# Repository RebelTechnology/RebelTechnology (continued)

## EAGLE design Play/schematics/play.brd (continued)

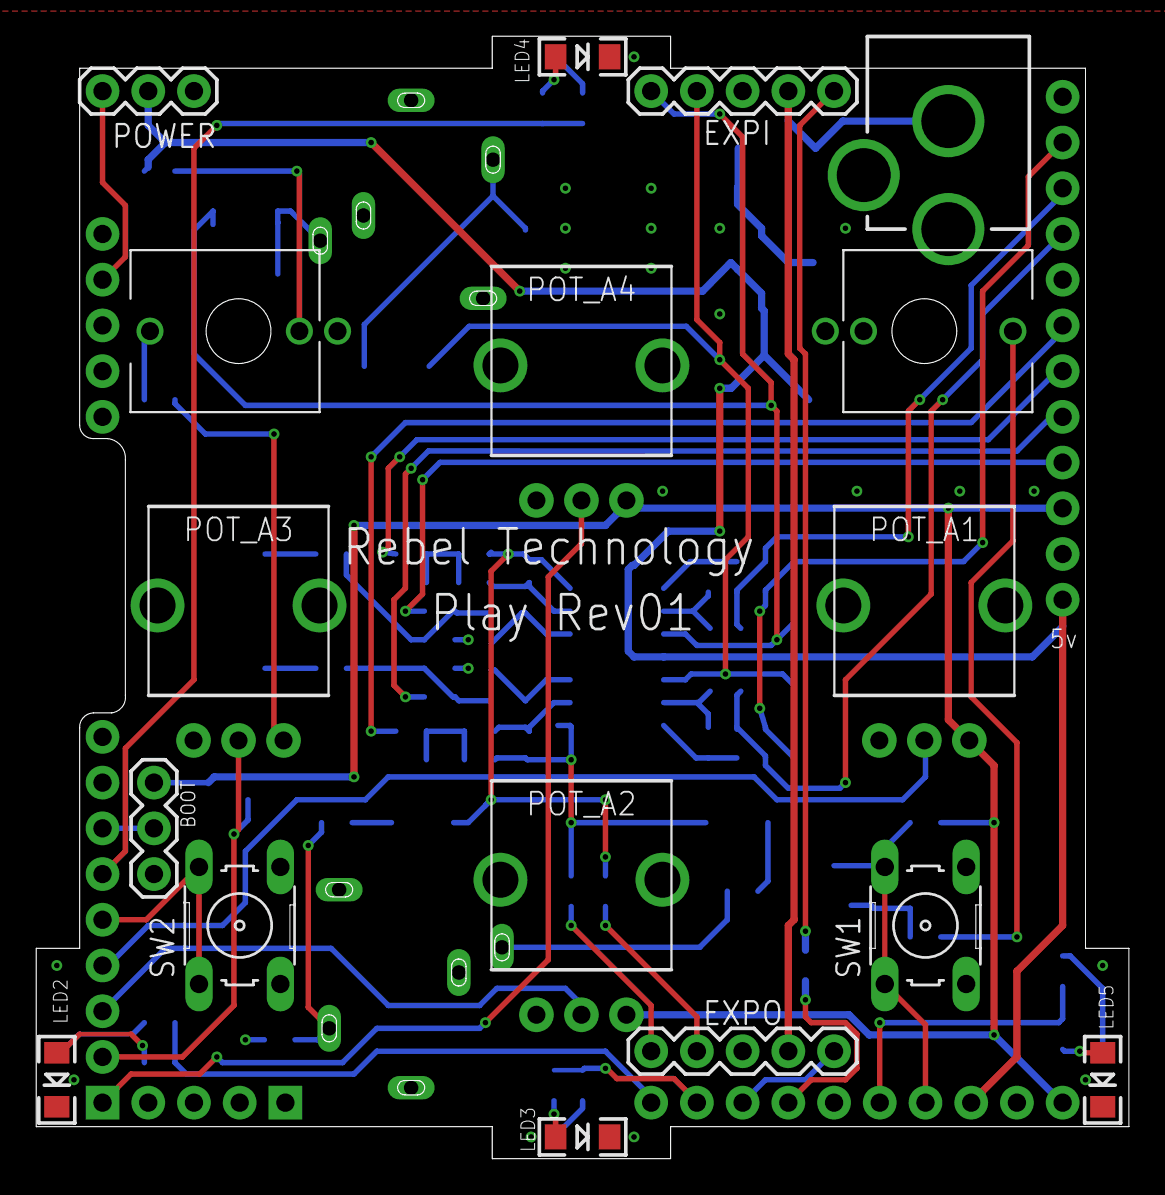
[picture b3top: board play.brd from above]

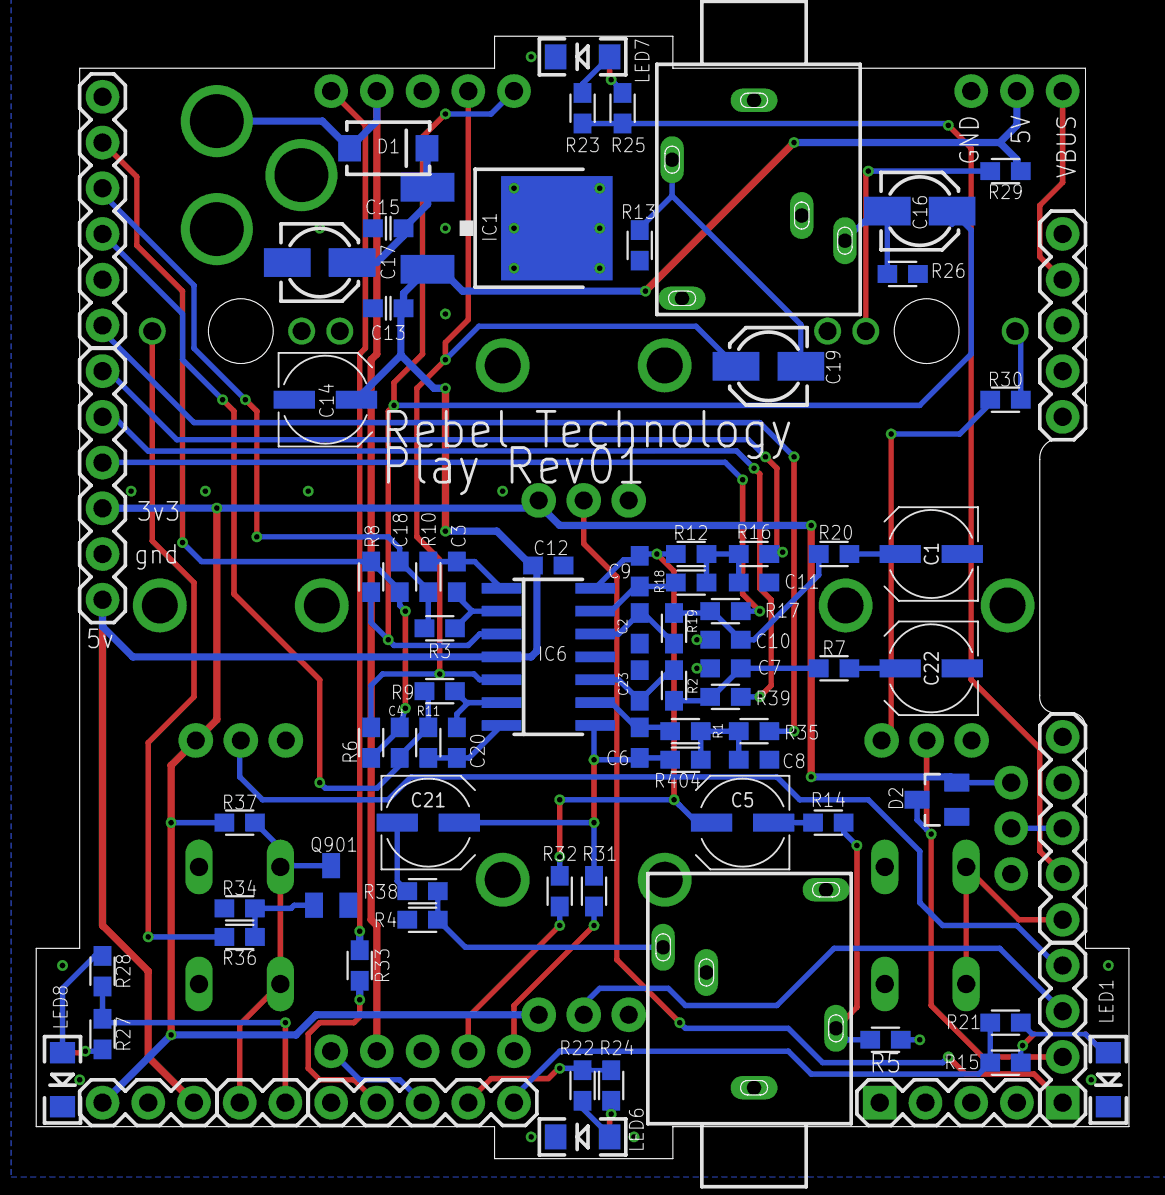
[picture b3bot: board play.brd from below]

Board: 2 copper layers, 60.7 x 62.4 mm, 100 parts (83 on the bottom side), 66 nets.

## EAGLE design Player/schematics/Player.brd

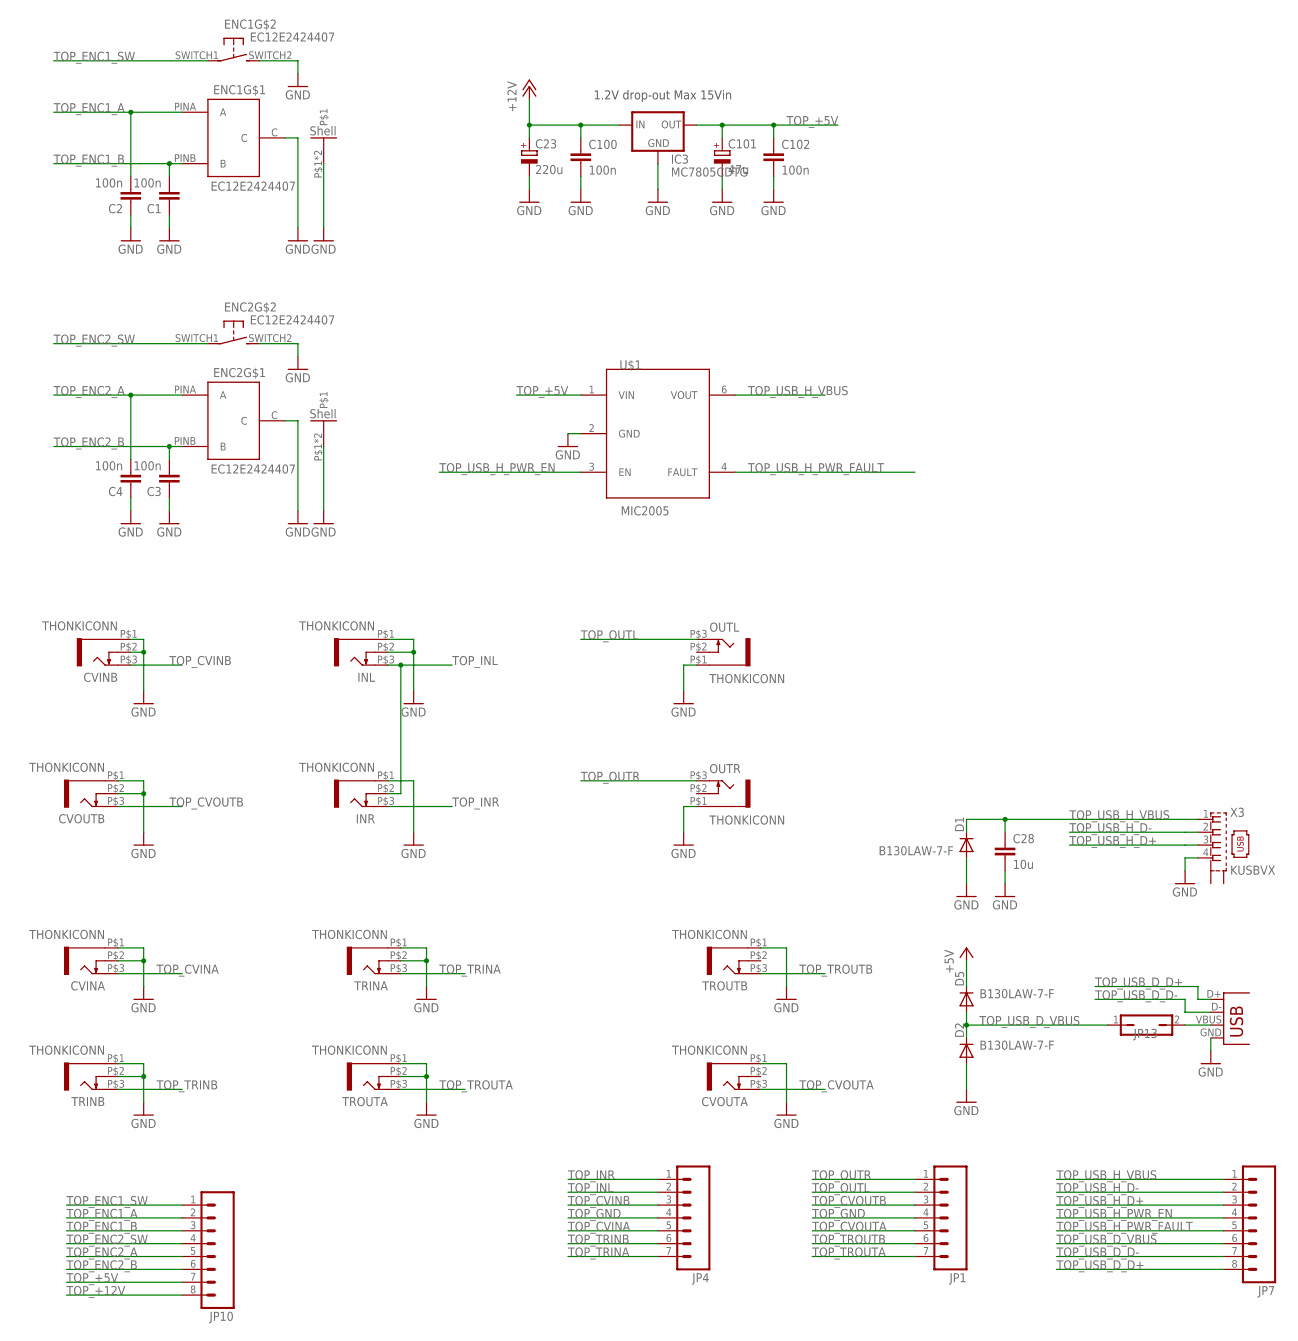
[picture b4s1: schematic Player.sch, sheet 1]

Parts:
C1, C2, C3, C4, C100, C102: 100n; C0603
C23: 220u; PANASONIC_D
C28: 10u; C1206
C101: 47u; CPOL-5
CVINA: THONKICONN
CVINB: THONKICONN
CVOUTA: THONKICONN
CVOUTB: THONKICONN
D1, D2, D5: B130LAW-7-F; SOD123
ENC1, ENC2: EC12E2424407
IC3: MC7805CDTG; DPACK
INL: THONKICONN
INR: THONKICONN
JP1, JP4: M07; 1X07
JP7, JP10: M081X08; 1X08
JP13: JP1Q; JP1
OUTL: THONKICONN
OUTR: THONKICONN
TRINA: THONKICONN
TRINB: THONKICONN
TROUTA: THONKICONN
TROUTB: THONKICONN
U$1: MIC2005; SOT23-6
X3: KUSBVX
X5: USBPTH-VERTICAL; USB-B-PTH-VERTICAL

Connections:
unnamed: JP13.2, X5.VBUS
TOP_+5V: C101.+, C102.1, D5.C, IC3.3 (OUT), JP10.7, U$1.1 (VIN)
TOP_+12V: C23.+, C100.1, IC3.1 (IN), JP10.8
TOP_CVINA: CVINA.P$3 (3), JP4.5
TOP_CVINB: CVINB.P$3 (3), JP4.3
TOP_CVOUTA: CVOUTA.P$3 (3), JP1.5
TOP_CVOUTB: CVOUTB.P$3 (3), JP1.3
TOP_ENC1_A: C2.2, ENC1.PINA (A), JP10.2
TOP_ENC1_B: C1.2, ENC1.PINB (B), JP10.3
TOP_ENC1_SW: ENC1.SWITCH1, JP10.1
TOP_ENC2_A: C4.2, ENC2.PINA (A), JP10.5
TOP_ENC2_B: C3.2, ENC2.PINB (B), JP10.6
TOP_ENC2_SW: ENC2.SWITCH1, JP10.4
TOP_GND: C1.1, C2.1, C3.1, C4.1, C23.-, C28.2, C100.2, C101.-, C102.2, CVINA.P$1 (5), CVINA.P$2 (4), CVINB.P$1 (5), CVINB.P$2 (4), CVOUTA.P$1 (5), CVOUTB.P$1 (5), CVOUTB.P$2 (4), D1.A, D2.A, ENC1.C, ENC1.P$1, ENC1.P$2, ENC1.SWITCH2 (S), ENC2.C, ENC2.P$1, ENC2.P$2, ENC2.SWITCH2 (S), IC3.4 (GND), INL.P$1 (5), INL.P$2 (4), INR.P$1 (5), JP1.4, JP4.4, OUTL.P$1 (5), OUTR.P$1 (5), TRINA.P$1 (5), TRINA.P$2 (4), TRINB.P$1 (5), TRINB.P$2 (4), TROUTA.P$1 (5), TROUTA.P$2 (4), TROUTB.P$1 (5), U$1.2 (GND), X3.4, X5.GND
TOP_INL: INL.P$3 (3), INR.P$2 (4), JP4.2
TOP_INR: INR.P$3 (3), JP4.1
TOP_OUTL: JP1.2, OUTL.P$3 (3)
TOP_OUTR: JP1.1, OUTR.P$3 (3)
TOP_TRINA: JP4.7, TRINA.P$3 (3)
TOP_TRINB: JP4.6, TRINB.P$3 (3)
TOP_TROUTA: JP1.7, TROUTA.P$3 (3)
TOP_TROUTB: JP1.6, TROUTB.P$3 (3)
TOP_USB_D_D+: JP7.8, X5.D+
TOP_USB_D_D-: JP7.7, X5.D-
TOP_USB_D_VBUS: D2.C, D5.A, JP7.6, JP13.1
TOP_USB_H_D+: JP7.3, X3.3
TOP_USB_H_D-: JP7.2, X3.2
TOP_USB_H_PWR_EN: JP7.4, U$1.3 (EN)
TOP_USB_H_PWR_FAULT: JP7.5, U$1.4 (FAULT)
TOP_USB_H_VBUS: C28.1, D1.C, JP7.1, U$1.6 (VOUT), X3.1

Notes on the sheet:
1.2V drop-out Max 15Vin

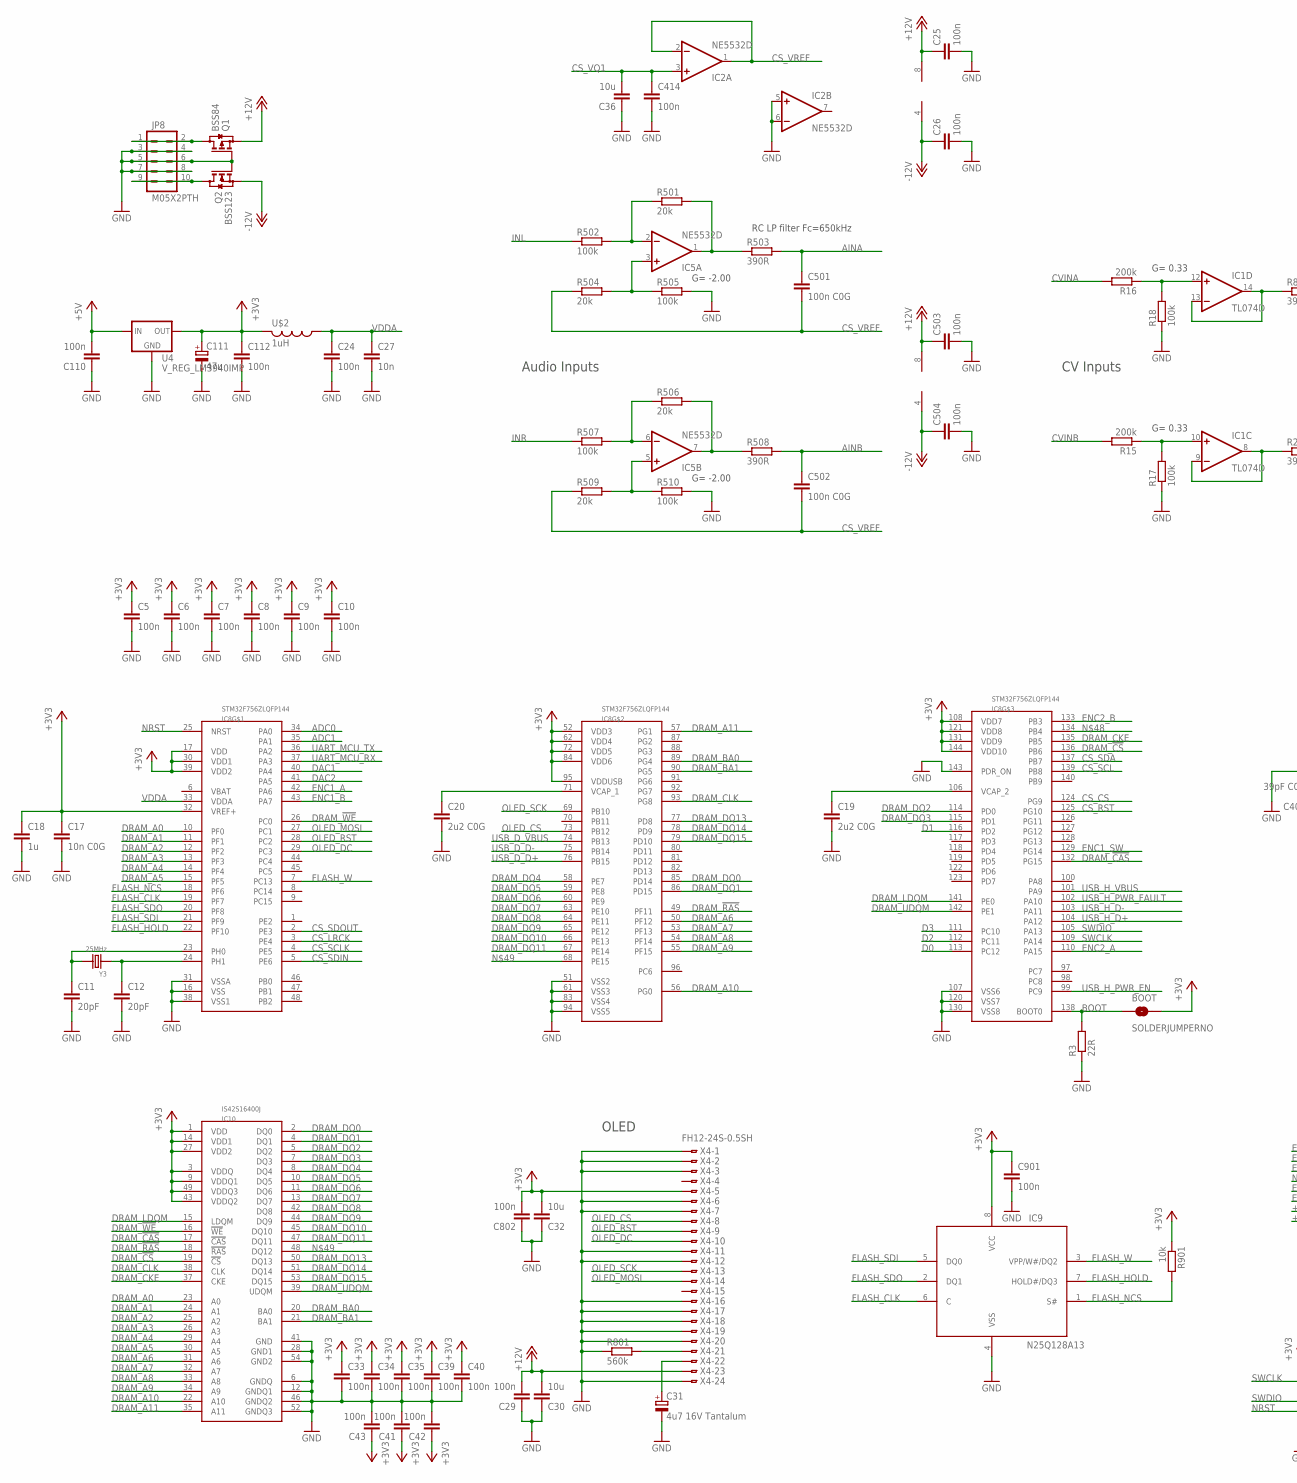
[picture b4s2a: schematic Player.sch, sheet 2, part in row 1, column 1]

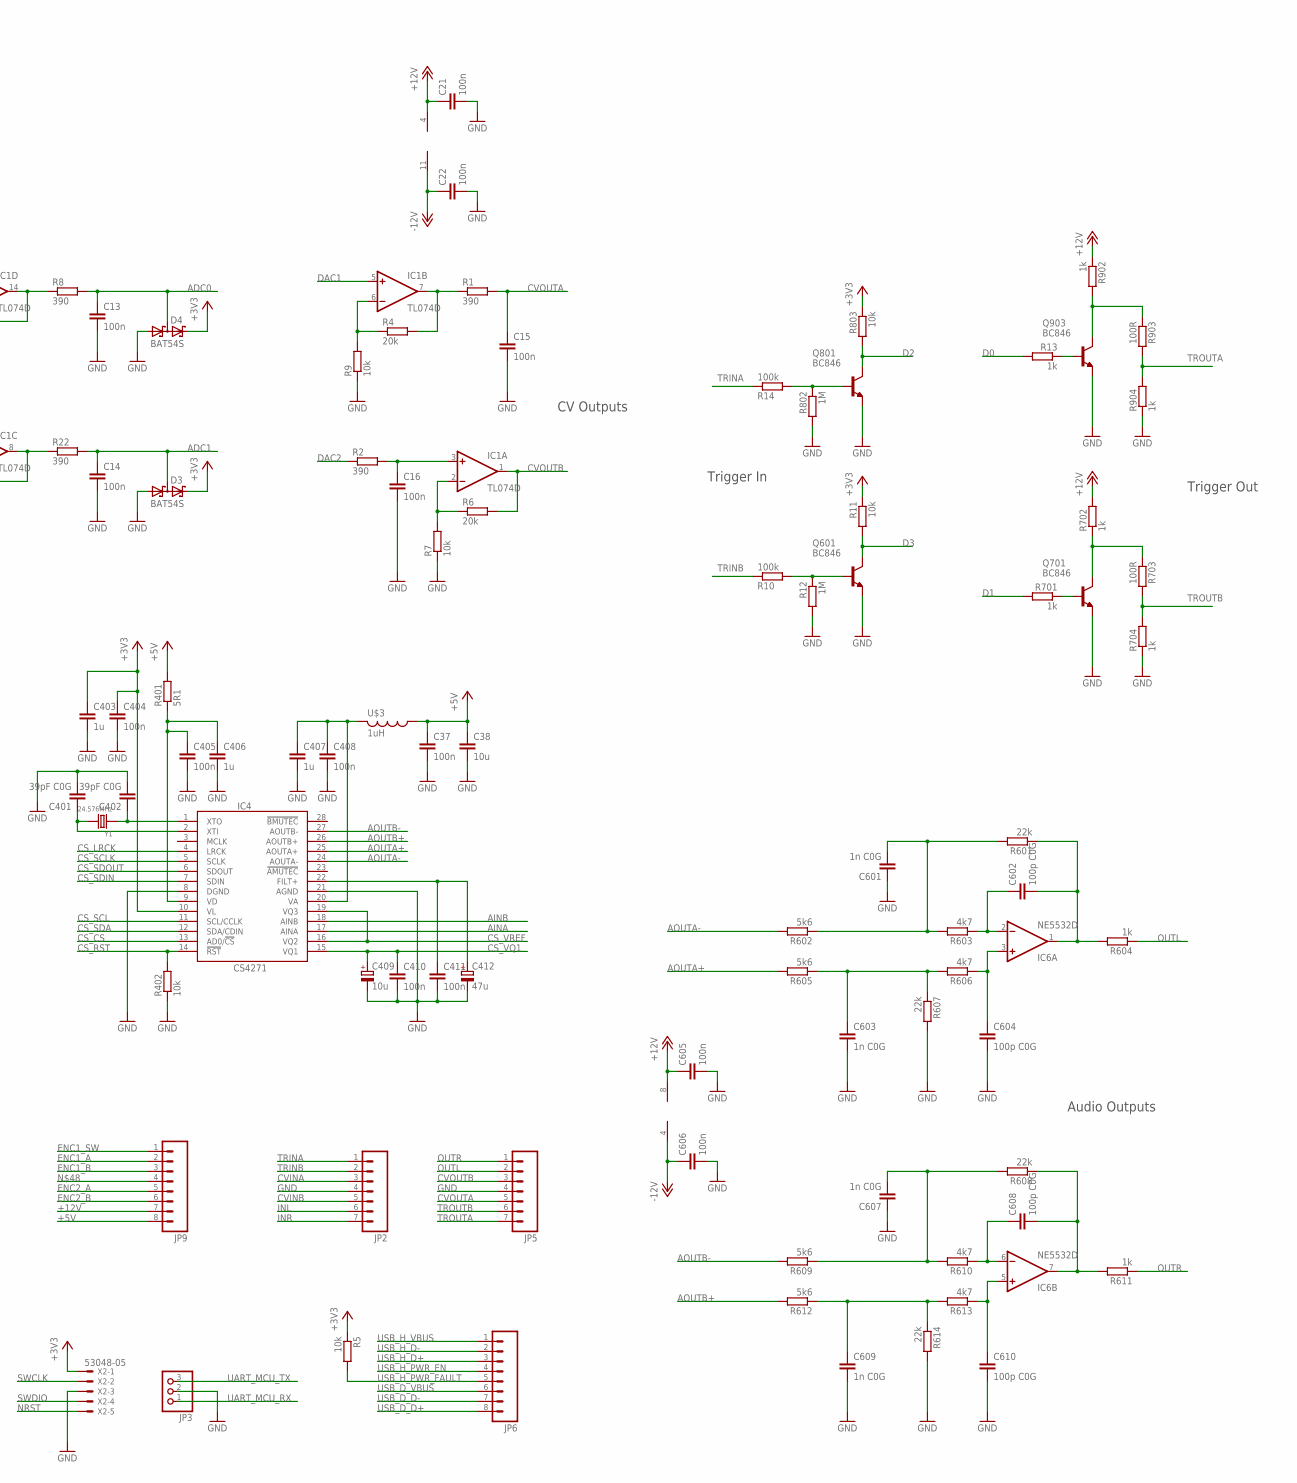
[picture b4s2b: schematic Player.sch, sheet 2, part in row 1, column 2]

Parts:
BOOT: SOLDERJUMPERNO; SJ_2S-NO
C5, C6, C7, C8, C9, C10, C13, C14, C15, C16, C21, C22, C24, C25, C26, C29, C33, C34, C35, C37, C39, C40, C41, C42, C43, C110, C112, C404, C405, C408, C410, C411, C414, C503, C504, C605, C606, C802, C901: 100n; C0603
C11, C12: 20pF; C0603
C17: 10n C0G; C0603
C18, C403, C406, C407: 1u; C0603
C19, C20: 2u2 C0G; C0603
C27: 10n; C0603
C30, C32, C36: 10u; C1206
C31: 4u7 16V Tantalum; SMC_A
C38: 10u; C0603
C111, C412: 47u; CPOL-5
C401, C402: 39pF C0G; C0603
C409: 10u; CPOL-5
C501, C502: 100n C0G; C0603
C601, C603, C607, C609: 1n C0G; C0603
C602, C604, C608, C610: 100p C0G; C0603
D3, D4: BAT54S; SOT23
IC1: TL074D; SO14
IC2, IC5, IC6: NE5532D; SO08
IC4: CS4271; TSSOP28-0.65-9.7X4.4MM
IC8: STM32F756ZLQFP144; QFP50P2200X2200X160-144N
IC9: N25Q128A13; SO8W
IC10: IS42S16400J; TSOP54-400
JP2, JP5: M07; 1X07
JP3: CON-JST-1X03PH-TH; JST-B3B-PH-KL
JP6, JP9: M081X08; 1X08
JP8: M05X2PTH; AVR_ICSP
Q1: BSS84; SOT23
Q2: BSS123; SOT23
Q601, Q701, Q801, Q903: BC846; SOT23
R1, R2, R8, R22: 390; 0603
R3: 22R; 0603
R4, R6, R501, R504, R506, R509: 20k; 0603
R5, R7, R9, R11, R402, R803, R901: 10k; 0603
R10, R14, R17, R18, R502, R505, R507, R510: 100k; 0603
R12, R802: 1M; 0603
R13, R604, R611, R701, R702, R704, R902, R904: 1k; 0603
R15, R16: 200k; 0603
R401: 5R1; 0603
R503, R508: 390R; 0603
R601, R607, R608, R614: 22k; 0603
R602, R605, R609, R612: 5k6; 0603
R603, R606, R610, R613: 4k7; 0603
R703, R903: 100R; 0603
R801: 560k; 0603
U4: V_REG_LM3940IMP; SOT223
U$2, U$3: 1uH; 0603
X2: 53048-05
X4: FH12-24S-0.5SH
Y1: 24.576MHz; X2-SMD-5.0X3.2X1.3MM
Y3: 25MHz; X2-SMD-5.0X3.2X1.3MM

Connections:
+3.3V: BOOT.2, C5.1, C6.1, C7.1, C8.1, C9.1, C10.1, C17.1, C18.1, C32.2, C33.1, C34.1, C35.1, C39.1, C40.1, C41.1, C42.1, C43.1, C111.+, C112.1, C403.1, C404.1, C802.2, C901.1, D3.2 (C2), D4.2 (C2), IC4.10 (VL), IC8.17 (VDD), IC8.30 (VDD1), IC8.32 (VREF+), IC8.39 (VDD2), IC8.52 (VDD3), IC8.62 (VDD4), IC8.72 (VDD5), IC8.84 (VDD6), IC8.95 (VDDUSB), IC8.108 (VDD7), IC8.121 (VDD8), IC8.131 (VDD9), IC8.144 (VDD10), IC9.8 (VCC), IC10.1 (VDD), IC10.3 (VDDQ), IC10.9 (VDDQ1), IC10.14 (VDD1), IC10.27 (VDD2), IC10.43 (VDDQ2), IC10.49 (VDDQ3), R5.1, R11.1, R803.1, R901.1, U4.3 (OUT), U$2.2, X2.1, X4.5
+5V: C37.1, C38.1, C110.2, JP9.8, R401.2, U4.1 (IN), U$3.1
+12V: C21.1, C25.1, C29.2, C30.2, C503.1, C605.1, IC1.4 (V+), IC2.8 (V+), IC5.8 (V+), IC6.8 (V+), JP9.7, Q1.2 (S), R702.2, R902.1, X4.23
-12V: C22.1, C26.1, C504.1, C606.1, IC1.11 (V-), IC2.4 (V-), IC5.4 (V-), IC6.4 (V-), Q2.2 (S)
ADC0: C13.1, D4.3 (C1A2), IC8.34 (PA0), R8.2
ADC1: C14.1, D3.3 (C1A2), IC8.35 (PA1), R22.2
AINA: C501.1, IC4.17 (AINA), R503.2
AINB: C502.1, IC4.18 (AINB), R508.2
ANALOG_OUTA: C602.2, IC6.1 (OUT), R601.1, R604.2
ANALOG_OUTB: C608.2, IC6.7 (OUT), R608.1, R611.2
AOUTA+: IC4.25 (AOUTA+), R605.2
AOUTA-: IC4.24 (AOUTA-), R602.2
AOUTB+: IC4.26 (AOUTB+), R612.2
AOUTB-: IC4.27 (AOUTB-), R609.2
BOOT: BOOT.1, IC8.138 (BOOT0), R3.2
CS_CS: IC4.13 (AD0/!CS), IC8.124 (PG9)
CS_LRCK: IC4.4 (LRCK), IC8.3 (PE4)
CS_RST: IC4.14 (!RST), IC8.125 (PG10), R402.2
CS_SCL: IC4.11 (SCL/CCLK), IC8.139 (PB8)
CS_SCLK: IC4.5 (SCLK), IC8.4 (PE5)
CS_SDA: IC4.12 (SDA/CDIN), IC8.137 (PB7)
CS_SDIN: IC4.7 (SDIN), IC8.5 (PE6)
CS_SDOUT: IC4.6 (SDOUT), IC8.2 (PE3)
CS_VQ1: C36.2, C409.+, C410.1, C414.1, IC2.3 (+IN), IC4.15 (VQ1)
CS_VREF: C501.2, C502.2, IC2.1 (OUT), IC2.2 (-IN), IC4.16 (VQ2), IC4.19 (VQ3), R504.1, R509.1
CVINA: JP2.3, R16.2
CVINB: JP2.5, R15.2
CVOUTA: C15.1, JP5.5, R1.2
CVOUTB: IC1.1 (OUT), JP5.3, R6.2
D0: IC8.113 (PC12), R13.2
D1: IC8.116 (PD2), R701.2
D2: IC8.112 (PC11), Q801.3 (C), R803.2
D3: IC8.111 (PC10), Q601.3 (C), R11.2
DAC1: IC1.5 (+IN), IC8.40 (PA4)
DAC2: IC8.41 (PA5), R2.1
DRAM_!CAS: IC8.132 (PG15), IC10.17 (!CAS)
DRAM_!CS: IC8.136 (PB6), IC10.19 (!CS)
DRAM_!RAS: IC8.49 (PF11), IC10.18 (!RAS)
DRAM_!WE: IC8.26 (PC0), IC10.16 (!WE)
DRAM_A0: IC8.10 (PF0), IC10.23 (A0)
DRAM_A1: IC8.11 (PF1), IC10.24 (A1)
DRAM_A2: IC8.12 (PF2), IC10.25 (A2)
DRAM_A3: IC8.13 (PF3), IC10.26 (A3)
DRAM_A4: IC8.14 (PF4), IC10.29 (A4)
DRAM_A5: IC8.15 (PF5), IC10.30 (A5)
DRAM_A6: IC8.50 (PF12), IC10.31 (A6)
DRAM_A7: IC8.53 (PF13), IC10.32 (A7)
DRAM_A8: IC8.54 (PF14), IC10.33 (A8)
DRAM_A9: IC8.55 (PF15), IC10.34 (A9)
DRAM_A10: IC8.56 (PG0), IC10.22 (A10)
DRAM_A11: IC8.57 (PG1), IC10.35 (A11)
DRAM_BA0: IC8.89 (PG4), IC10.20 (BA0)
DRAM_BA1: IC8.90 (PG5), IC10.21 (BA1)
DRAM_CKE: IC8.135 (PB5), IC10.37 (CKE)
DRAM_CLK: IC8.93 (PG8), IC10.38 (CLK)
DRAM_DQ0: IC8.85 (PD14), IC10.2 (DQ0)
DRAM_DQ1: IC8.86 (PD15), IC10.4 (DQ1)
DRAM_DQ2: IC8.114 (PD0), IC10.5 (DQ2)
DRAM_DQ3: IC8.115 (PD1), IC10.7 (DQ3)
DRAM_DQ4: IC8.58 (PE7), IC10.8 (DQ4)
DRAM_DQ5: IC8.59 (PE8), IC10.10 (DQ5)
DRAM_DQ6: IC8.60 (PE9), IC10.11 (DQ6)
DRAM_DQ7: IC8.63 (PE10), IC10.13 (DQ7)
DRAM_DQ8: IC8.64 (PE11), IC10.42 (DQ8)
DRAM_DQ9: IC8.65 (PE12), IC10.44 (DQ9)
DRAM_DQ10: IC8.66 (PE13), IC10.45 (DQ10)
DRAM_DQ11: IC8.67 (PE14), IC10.47 (DQ11)
DRAM_DQ13: IC8.77 (PD8), IC10.50 (DQ13)
DRAM_DQ14: IC8.78 (PD9), IC10.51 (DQ14)
DRAM_DQ15: IC8.79 (PD10), IC10.53 (DQ15)
DRAM_LDQM: IC8.141 (PE0), IC10.15 (LDQM)
DRAM_UDQM: IC8.142 (PE1), IC10.39 (UDQM)
ENC1_A: IC8.42 (PA6), JP9.2
ENC1_B: IC8.43 (PA7), JP9.3
ENC1_SW: IC8.129 (PG14), JP9.1
ENC2_A: IC8.110 (PA15), JP9.5
ENC2_B: IC8.133 (PB3), JP9.6
FLASH_CLK: IC8.19 (PF7), IC9.6 (C)
FLASH_HOLD: IC8.22 (PF10), IC9.7 (HOLD#/DQ3)
FLASH_NCS: IC8.18 (PF6), IC9.1 (S#), R901.2
FLASH_SDI: IC8.21 (PF9), IC9.5 (DQ0)
FLASH_SDO: IC8.20 (PF8), IC9.2 (DQ1)
FLASH_W: IC8.7 (PC13), IC9.3 (VPP/W#/DQ2)
GND: C5.2, C6.2, C7.2, C8.2, C9.2, C10.2, C11.2, C12.2, C13.2, C14.2, C15.2, C16.2, C17.2, C18.2, C19.2, C20.2, C21.2, C22.2, C24.2, C25.2, C26.2, C27.2, C29.1, C30.1, C31.-, C32.1, C33.2, C34.2, C35.2, C36.1, C37.2, C38.2, C39.2, C40.2, C41.2, C42.2, C43.2, C110.1, C111.-, C112.2, C401.2, C402.2, C403.2, C404.2, C405.2, C406.2, C407.2, C408.2, C409.-, C410.2, C411.2, C412.-, C414.2, C503.2, C504.2, C601.1, C603.2, C604.2, C605.2, C606.2, C607.1, C609.2, C610.2, C802.1, C901.2, D3.1 (A1), D4.1 (A1), IC2.5 (+IN), IC2.6 (-IN), IC4.8 (DGND), IC4.21 (AGND), IC8.16 (VSS), IC8.31 (VSSA), IC8.38 (VSS1), IC8.51 (VSS2), IC8.61 (VSS3), IC8.83 (VSS4), IC8.94 (VSS5), IC8.107 (VSS6), IC8.120 (VSS7), IC8.130 (VSS8), IC8.143 (PDR_ON), IC9.4 (VSS), IC10.6 (GNDQ), IC10.12 (GNDQ1), IC10.28 (GND1), IC10.41 (GND), IC10.46 (GNDQ2), IC10.52 (GNDQ3), IC10.54 (GND2), JP2.4, JP3.2, JP5.4, JP8.3, JP8.4, JP8.5, JP8.6, JP8.7, JP8.8, Q1.1 (G), Q2.1 (G), Q601.2 (E), Q701.2 (E), Q801.2 (E), Q903.2 (E), R3.1, R7.1, R9.1, R12.2, R17.1, R18.1, R402.1, R505.2, R510.2, R607.2, R614.2, R704.1, R801.1, R802.2, R904.1, U4.2 (GND), X2.3, X4.1, X4.2, X4.3, X4.6, X4.7, X4.11, X4.12, X4.16, X4.17, X4.18, X4.19, X4.20, X4.24
INL: JP2.6, R502.1
INR: JP2.7, R507.1
unnamed: C603.1, R605.1, R606.2, R607.1
unnamed: IC1.12 (+IN), R16.1, R18.2
unnamed: C407.1, C408.1, IC4.20 (VA), U$3.2
unnamed: IC1.7 (OUT), R1.1, R4.2
unnamed: IC1.8 (OUT), IC1.9 (-IN), R22.1
unnamed: C31.+, X4.22
unnamed: JP8.9, JP8.10, Q2.3 (D)
unnamed: R801.2, X4.21
unnamed: JP8.1, JP8.2, Q1.3 (D)
unnamed: C601.2, R601.2, R602.1, R603.2
unnamed: C12.1, IC8.24 (PH1), Y3.1
unnamed: IC1.2 (-IN), R6.1, R7.2
unnamed: C602.1, IC6.2 (-IN), R603.1
unnamed: C604.1, IC6.3 (+IN), R606.1
unnamed: IC1.6 (-IN), R4.1, R9.2
unnamed: C11.1, IC8.23 (PH0), Y3.2
unnamed: C402.1, IC4.1 (XTO), Y1.1
unnamed: C411.1, C412.+, IC4.22 (FILT+)
unnamed: C401.1, IC4.2 (XTI), Y1.2
unnamed: C609.1, R612.1, R613.2, R614.1
unnamed: C607.2, R608.2, R609.1, R610.2
unnamed: C608.1, IC6.6 (-IN), R610.1
unnamed: C610.1, IC6.5 (+IN), R613.1
unnamed: IC1.13 (-IN), IC1.14 (OUT), R8.1
unnamed: C16.1, IC1.3 (+IN), R2.2
unnamed: C19.1, IC8.106 (VCAP_2)
unnamed: C20.1, IC8.71 (VCAP_1)
unnamed: IC5.3 (+IN), R504.2, R505.1
unnamed: Q601.1 (B), R10.2, R12.1
unnamed: IC5.2 (-IN), R501.1, R502.2
unnamed: Q701.1 (B), R701.1
unnamed: IC5.1 (OUT), R501.2, R503.1
unnamed: Q701.3 (C), R702.1, R703.1
unnamed: IC5.5 (+IN), R509.2, R510.1
unnamed: IC5.6 (-IN), R506.1, R507.2
unnamed: IC5.7 (OUT), R506.2, R508.1
unnamed: IC1.10 (+IN), R15.1, R17.2
unnamed: Q903.1 (B), R13.1
unnamed: IC8.134 (PB4), JP9.4
unnamed: IC8.68 (PE15), IC10.48 (DQ12)
unnamed: Q903.3 (C), R902.2, R903.1
unnamed: Q801.1 (B), R14.2, R802.1
NRST: IC8.25 (NRST), X2.5
OLED_CS: IC8.73 (PB12), X4.8
OLED_DC: IC8.29 (PC3), X4.10
OLED_MOSI: IC8.27 (PC1), X4.14
OLED_RST: IC8.28 (PC2), X4.9
OLED_SCK: IC8.69 (PB10), X4.13
OUTL: JP5.2, R604.1
OUTR: JP5.1, R611.1
SWCLK: IC8.109 (PA14), X2.2
SWDIO: IC8.105 (PA13), X2.4
TRINA: JP2.1, R14.1
TRINB: JP2.2, R10.1
TROUTA: JP5.7, R903.2, R904.2
TROUTB: JP5.6, R703.2, R704.2
UART_MCU_RX: IC8.37 (PA3), JP3.1
UART_MCU_TX: IC8.36 (PA2), JP3.3
USB_D_D+: IC8.76 (PB15), JP6.8
USB_D_D-: IC8.75 (PB14), JP6.7
USB_D_VBUS: IC8.74 (PB13), JP6.6
USB_H_D+: IC8.104 (PA12), JP6.3
USB_H_D-: IC8.103 (PA11), JP6.2
USB_H_PWR_EN: IC8.99 (PC9), JP6.4
USB_H_PWR_FAULT: IC8.102 (PA10), JP6.5, R5.2
USB_H_VBUS: IC8.101 (PA9), JP6.1
VD: C405.1, C406.1, IC4.9 (VD), R401.1
VDDA: C24.1, C27.1, IC8.33 (VDDA), U$2.1

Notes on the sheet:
RC LP filter Fc=650kHz
Audio Outputs
Audio Inputs
CV Inputs
G= -2.00
G= 0.33
CV Outputs
Trigger In
Trigger Out
OLED

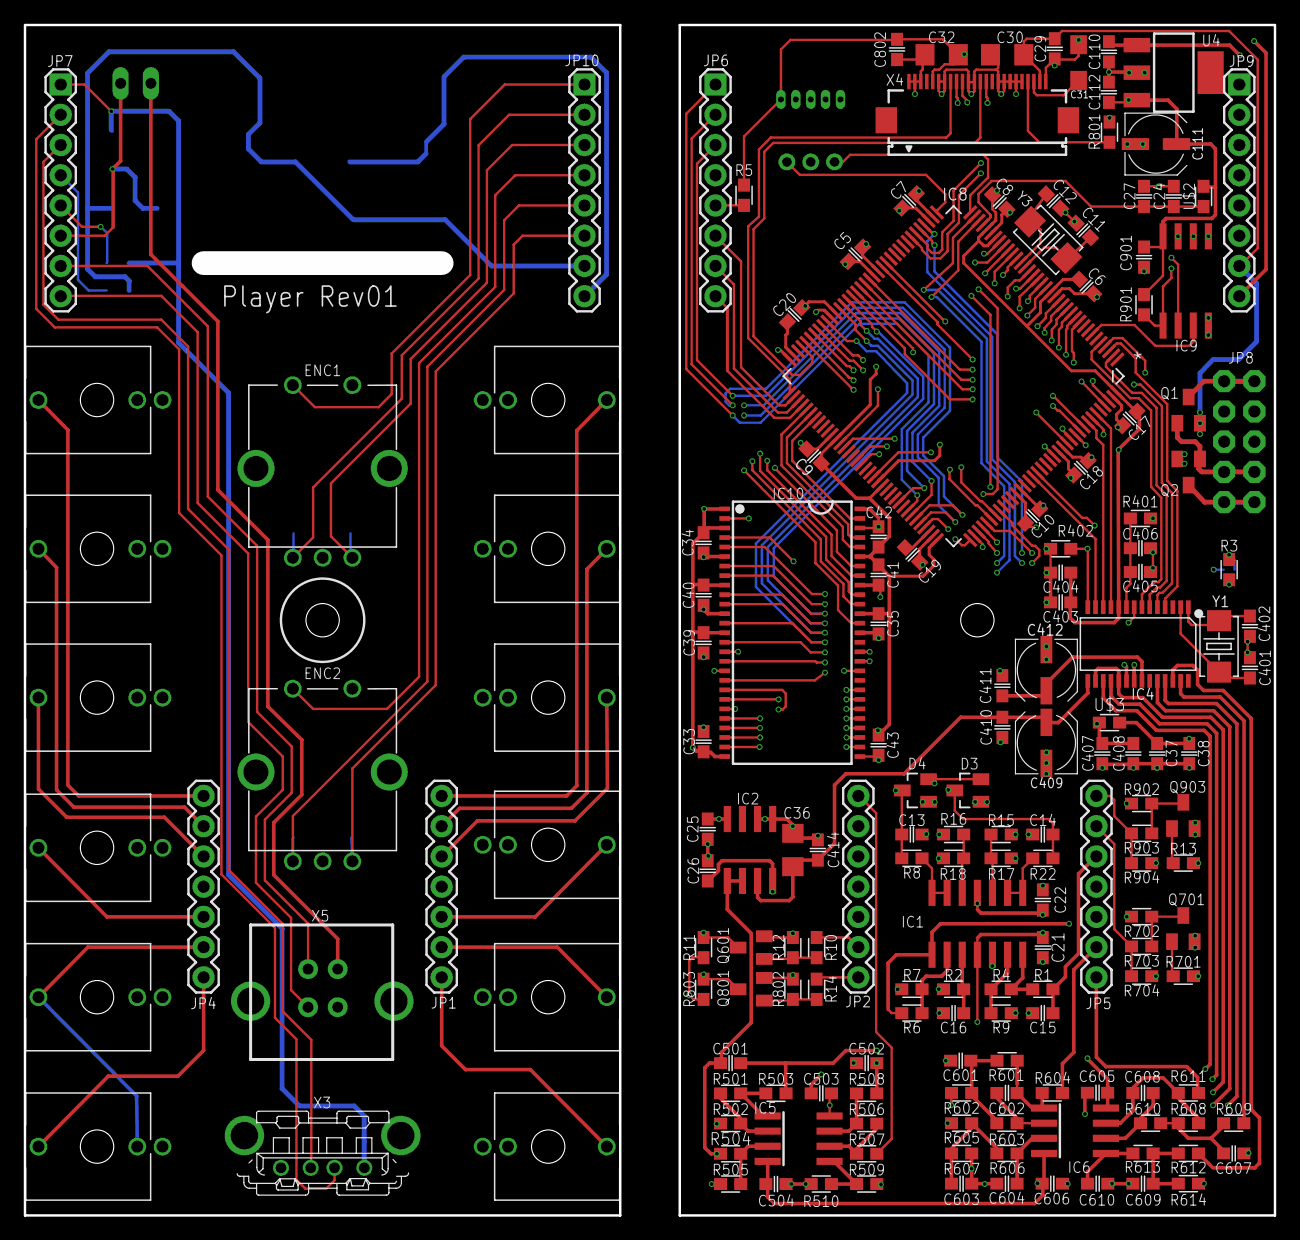
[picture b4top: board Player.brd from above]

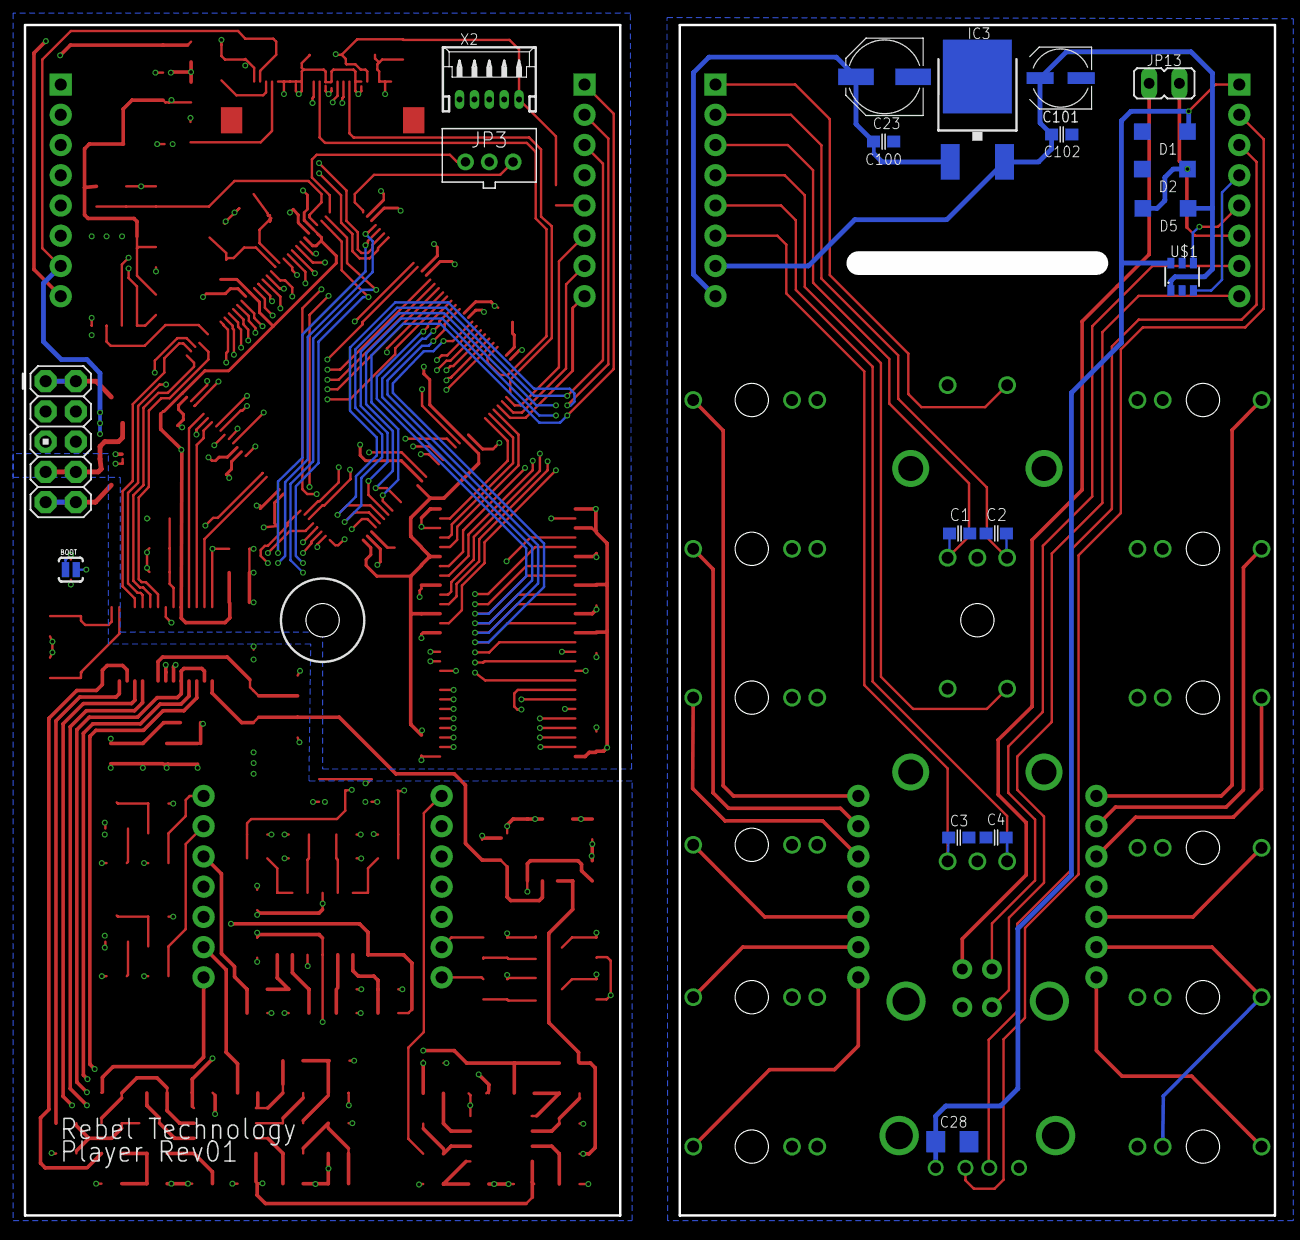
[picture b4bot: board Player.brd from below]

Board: 4 copper layers, 50.0 x 100.0 mm, 190 parts (19 on the bottom side), 184 nets.
